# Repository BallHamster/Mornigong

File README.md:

# Mornigong
A morning clock that wakes you up with a sound of a gong/marimba!

## How it works
This project uses 10 solenoids, a solenoid driver board (made by me), an esp32-c3 for controlling the solenoids, and a holder board (for my specific marimba and my solenoids)

Actual marimba and solenoids for my project

3d design of the driver board
## How to make it:
- 3d print 10 of the "part_studio.stl" files, and assemble them following "assembly.step"
- Fasten the solenoids to the 3d printed frame, and the frame to your marimba
- Wire the solenoids to the driver board
- Upload gong.ino to the esp32c3, and change the pins for your exact wiring.
- Play around!

### Print settings
- Use your preferred printer's basic settings (Like: https://craftlayerindia.com/blogs/3d-printer-settings/best-pla-settings-for-3d-printing)
- Leave supports off
- Infill: 15 %
- Print 10 of the parts, in batches or individually.
- Print in PLA

# IMPORTANT
- This is a two part project, I'm coming next week with the actual alarm clock, amd a more detailed program.

## BOM

| (Ref_no) | (Part name) | (Pcs) | (Link) | Price for needed parts/min order ($) |
| :--- | :--- | :--- | :--- | :--- |
| `-` | Solenoids | 10 | [AliExpress Link](https://aliexpress.com) | 15.00 |
| `-` | Marimba | 1 | [AliExpress Link](https://aliexpress.com) | 15.00 |
| `U1` | ESP32-C3 | 1 | [AliExpress Link](https://aliexpress.com?) | 3.00 |
| `C1` | 1000 uF 16V electrolytic, radial | 1 | [LCSC C43810](https://lcsc.com) | 0.80 |
| `C2, C3` | 100 nF 50V X7R, leaded MLCC | 2 | [LCSC C84772](https://lcsc.com) | 0.40 |
| `D1-D10` | 1N5408 rectifier, 3A 1000V, DO-201AD | 10 | [LCSC C2460](https://lcsc.com) | 0.85 |
| `F1` | PTC resettable fuse 3A hold / 6A trip, 30V | 1 | [LCSC C208487](https://lcsc.com) | 1.43 |
| `J1` | USB-C receptacle 16P, SMD + through-hole shell | 1 | [LCSC C165948](https://lcsc.com) | 0.87 |
| `J3-J12` | 2-position screw terminal, 5.0 mm pitch | 10 | [LCSC C474881](https://lcsc.com) | 1.03 |
| `Q10-Q19` | IRLZ44N logic-level MOSFET, TO-220AB | 10 | [LCSC C38774](https://lcsc.com) | 7.25 |
| `R1-R10` | 100 ohm 1/4W 5% carbon film, axial | 10 | [LCSC C120031](https://lcsc.com) | 0.59 |
| `R11-R20` | 10 kohm 1/4W 5% carbon film, axial | 10 | [LCSC C2894649](https://lcsc.com?) | 0.41 |
| `R21, R22` | 5.1 kohm 1/4W 5% carbon film, axial | 2 | [LCSC C120072](https://lcsc.com) | 0.57 |
| `-` | 3D printing costs | - | - | 2.50 |
| | | | **(Total cost):** | **49.70 \$** |

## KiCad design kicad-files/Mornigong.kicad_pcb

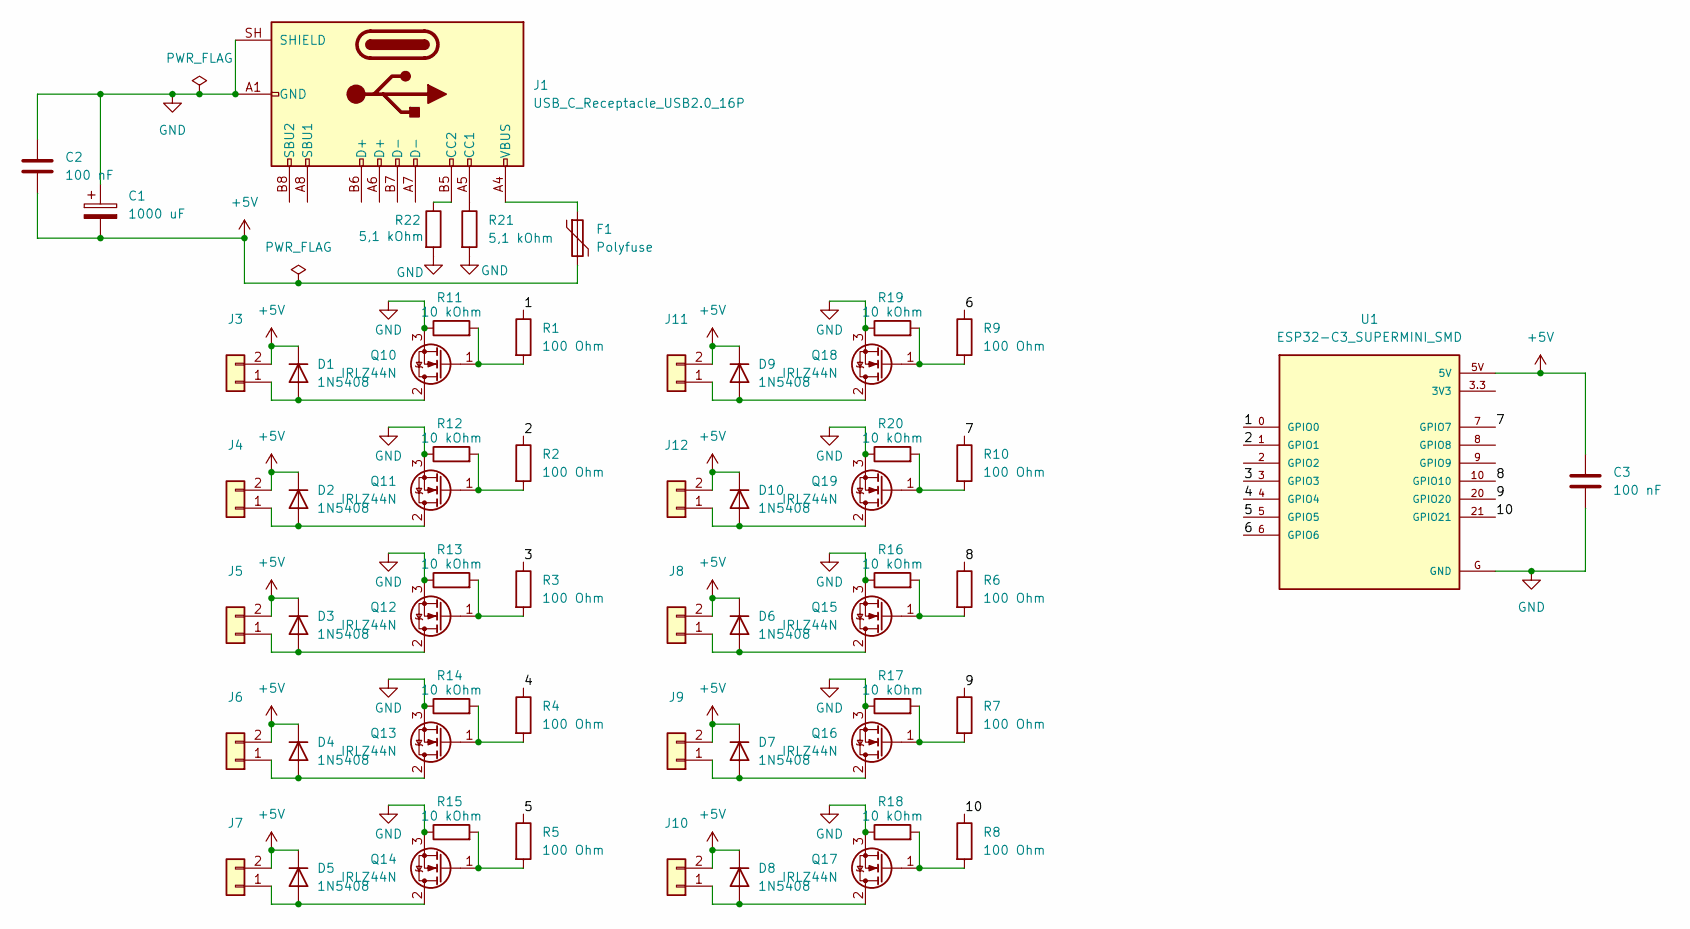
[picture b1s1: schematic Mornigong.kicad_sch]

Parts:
C1: 1000 uF; CP_Radial_D10.0mm_P5.00mm
C2, C3: 100 nF; C_Disc_D5.0mm_W2.5mm_P5.00mm
D1, D2, D3, D4, D5, D6, D7, D8, D9, D10: 1N5408; D_DO-201AD_P15.24mm_Horizontal
F1: Polyfuse; Fuse_Bourns_MF-RG300
J1: USB_C_Receptacle_USB2.0_16P; USB_C_Receptacle_HRO_TYPE-C-31-M-12
J3, J4, J5, J6, J7, J8, J9, J10, J11, J12: Conn_01x02; TerminalBlock_Phoenix_MKDS-1,5-2-5.08_1x02_P5.08mm_Horizont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
Q10, Q11, Q12, Q13, Q14, Q15, Q16, Q17, Q18, Q19: IRLZ44N; TO-220-3_Vertical
R1, R2, R3, R4, R5, R6, R7, R8, R9, R10: 100 Ohm; R_Axial_DIN0207_L6.3mm_D2.5mm_P10.16mm_Horizontal
R11, R12, R13, R14, R15, R16, R17, R18, R19, R20: 10 kOhm; R_Axial_DIN0207_L6.3mm_D2.5mm_P10.16mm_Horizontal
R21, R22: 5,1 kOhm; R_Axial_DIN0207_L6.3mm_D2.5mm_P10.16mm_Horizontal
U1: ESP32-C3_SUPERMINI_SMD; MODULE_ESP32-C3_SUPERMINI

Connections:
+5V: C1.2, C2.2, C3.1, D1.1 (K), D2.1 (K), D3.1 (K), D4.1 (K), D5.1 (K), D6.1 (K), D7.1 (K), D8.1 (K), D9.1 (K), D10.1 (K), F1.2, J3.2, J4.2, J5.2, J6.2, J7.2, J8.2, J9.2, J10.2, J11.2, J12.2, U1.5V
/1: R1.1, U1.0 (GPIO0)
/2: R2.1, U1.1 (GPIO1)
/3: R3.1, U1.3 (GPIO3)
/4: R4.1, U1.4 (GPIO4)
/5: R5.1, U1.5 (GPIO5)
/6: R9.1, U1.6 (GPIO6)
/7: R10.1, U1.7 (GPIO7)
/8: R6.1, U1.10 (GPIO10)
/9: R7.1, U1.20 (GPIO20)
/10: R8.1, U1.21 (GPIO21)
GND: C1.1, C2.1, C3.2, J1.A1 (GND), J1.A12 (GND), J1.B1 (GND), J1.B12 (GND), J1.SH (SHIELD), Q10.3 (S), Q11.3 (S), Q12.3 (S), Q13.3 (S), Q14.3 (S), Q15.3 (S), Q16.3 (S), Q17.3 (S), Q18.3 (S), Q19.3 (S), R11.1, R12.1, R13.1, R14.1, R15.1, R16.1, R17.1, R18.1, R19.1, R20.1, R21.2, R22.2, U1.G (GND)
unnamed: D1.2 (A), J3.1, Q10.2 (D)
unnamed: D2.2 (A), J4.1, Q11.2 (D)
unnamed: D3.2 (A), J5.1, Q12.2 (D)
unnamed: D4.2 (A), J6.1, Q13.2 (D)
unnamed: D5.2 (A), J7.1, Q14.2 (D)
unnamed: D6.2 (A), J8.1, Q15.2 (D)
unnamed: D7.2 (A), J9.1, Q16.2 (D)
unnamed: D8.2 (A), J10.1, Q17.2 (D)
unnamed: D9.2 (A), J11.1, Q18.2 (D)
unnamed: D10.2 (A), J12.1, Q19.2 (D)
unnamed: F1.1, J1.A4 (VBUS), J1.A9 (VBUS), J1.B4 (VBUS), J1.B9 (VBUS)
unnamed: J1.A5 (CC1), R21.1
unnamed: J1.B5 (CC2), R22.1
unnamed: Q10.1 (G), R1.2, R11.2
unnamed: Q11.1 (G), R2.2, R12.2
unnamed: Q12.1 (G), R3.2, R13.2
unnamed: Q13.1 (G), R4.2, R14.2
unnamed: Q14.1 (G), R5.2, R15.2
unnamed: Q15.1 (G), R6.2, R16.2
unnamed: Q16.1 (G), R7.2, R17.2
unnamed: Q17.1 (G), R8.2, R18.2
unnamed: Q18.1 (G), R9.2, R19.2
unnamed: Q19.1 (G), R10.2, R20.2

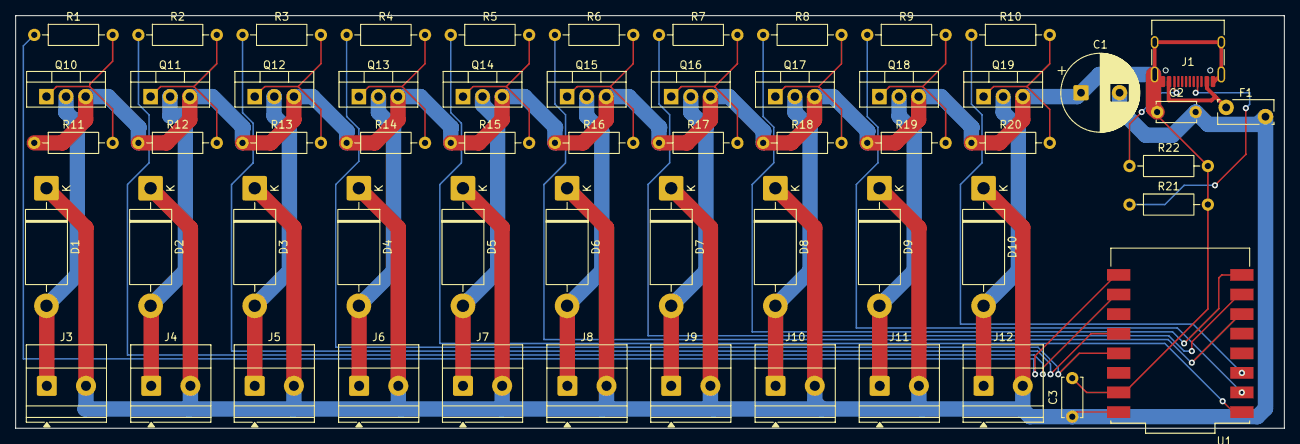
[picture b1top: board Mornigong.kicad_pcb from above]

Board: 2 copper layers, 164.5 x 53.5 mm, 58 parts (0 on the bottom side), 35 nets.
